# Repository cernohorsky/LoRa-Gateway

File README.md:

# LoRa-Gateway
Single channel LoRa gateway with RFM95W, ESP8266 and wide input DC-DC converter

#lora, #lorawan, #gateway, #esp8266, #rfm95

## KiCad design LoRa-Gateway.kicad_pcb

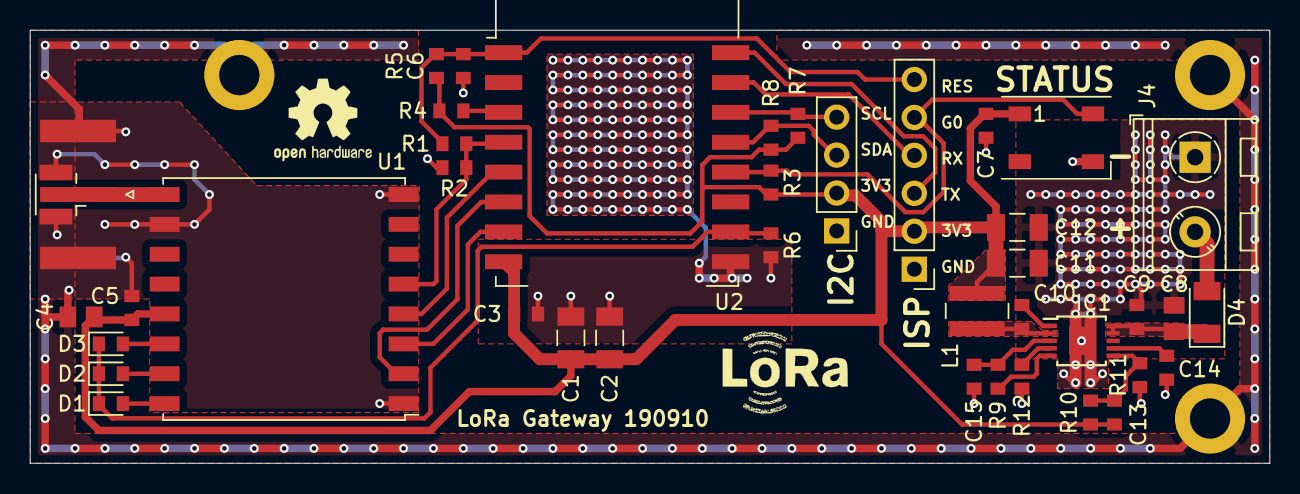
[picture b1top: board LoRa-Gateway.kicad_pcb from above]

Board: 2 copper layers, 83.0 x 29.0 mm, 44 parts (0 on the bottom side), 27 nets.

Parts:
C1, C2, C11, C12: 47u; C_1206_3216Metric
C3, C5, C7, C9: 100n; C_0603_1608Metric
C4, C8: 10u; C_0805_2012Metric
C6: 470p; C_0603_1608Metric
C10: 220n; C_0603_1608Metric
C13: 10p; C_0603_1608Metric
C14: 10n; C_0603_1608Metric
C15: 1u; C_0603_1608Metric
D1, D2, D3: D; D_0603_1608Metric
D4: D; D_1206_3216Metric
IC1: LT8609MSE; MSOP-10-1EP_3x3mm_P0.5mm_EP1.68x1.88mm
J1: Conn_Coaxial; SMA_Amphenol_132289_EdgeMount
J2: Conn_01x06; PinHeader_1x06_P2.54mm_Vertical
J3: Conn_01x04; PinHeader_1x04_P2.54mm_Vertical
J4: Conn_01x02; TerminalBlock_RND_205-00045_1x02_P5.00mm_Horizontal
J5, J6, J7: Conn_01x01; MountingHole_2.7mm_M2.5_DIN965_Pad
J8: Conn_Coaxial; U.FL_Hirose_U.FL-R-SMT-1_Vertical
L1: 3u3; L_Wuerth_MAPI-4020
LED1: WS2812B; LED_WS2812B_PLCC4_5.0x5.0mm_P3.2mm
R1: 470R; R_0603_1608Metric
R2: 100k; R_0603_1608Metric
R3, R4, R5, R6: 12k; R_0603_1608Metric
R7, R8: DNP; R_0603_1608Metric
R9: 0R; R_0603_1608Metric
R10: 220k; R_0603_1608Metric
R11: 68k; R_0603_1608Metric
R12: 18k; R_0603_1608Metric
U1: RFM95W-868S2; HOPERF_RFM95W_SMD
U2: ESP-12E

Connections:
+3V3: C1.1, C2.1, C3.1, C4.1, C5.1, C7.1, C11.1, C12.1, C13.1, J2.2, J3.2, L1.2, LED1.1, R3.2, R4.2, R5.2, R7.2, R8.2, R10.1, U1.13, U2.8
/ANT: J1.1, J8.1, U1.9
/CLK: U1.4, U2.5
/DIO0: D3.2, U1.14
/DIO1: D2.2, U1.15
/DIO2: D1.2, U1.16
/EN: R4.1, U2.3
/GPIO0: J2.5, LED1.4, R3.1, U2.18
/GPIO15: D1.1, D2.1, D3.1, R6.1, U2.16
/GPIO16: R1.1, R2.2, U1.5, U2.4
/MISO: U1.2, U2.6
/MOSI: U1.3, U2.7
/RES: C6.1, J2.6, R1.2, R5.1, U2.1
/RX: J2.4, U2.21
/SCL: J3.4, R7.1, U2.20
/SDA: J3.3, R8.1, U2.19
/TX: J2.3, U2.22
GND: C1.2, C2.2, C3.2, C4.2, C5.2, C6.2, C7.2, C8.2, C9.2, C11.2, C12.2, C14.2, C15.2, IC1.11, J1.2, J2.1, J3.1, J4.1, J5.1, J6.1, J7.1, J8.2, LED1.3, R2.1, R6.2, R11.1, R12.2, U1.1, U1.8, U1.10, U2.15
unnamed: C10.1, IC1.1
unnamed: C10.2, IC1.2, L1.1
unnamed: C13.2, IC1.6, R10.2, R11.2
unnamed: C14.1, IC1.7
unnamed: C15.1, IC1.3, R9.1
unnamed: D4.2, J4.2
unnamed: IC1.4, R12.1
unnamed: IC1.5, R9.2
VCC: C8.1, C9.1, D4.1, IC1.9, IC1.10

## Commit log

2019-08-30 Assigned footprints for main compennets
2019-08-30 Schematic finished, basic routing
2019-09-02 Changed barrel plug to terminal block
2019-09-03 Corrected feedback resistors values
2019-09-09 Routed DC-DC convertor, added vias under ESP8266 for better cooling
2019-09-10 Grounding improvement, dimmensions set
2019-09-11 Silk screen finished
2019-09-12 Edited mask under the ESP8266 for better cooling. Silkscreen improvement.
2019-09-13 Added protection diode, changed antenna connector
2019-09-16 Added Power flags, adden more vias around antenna connector, ERC, DRC
